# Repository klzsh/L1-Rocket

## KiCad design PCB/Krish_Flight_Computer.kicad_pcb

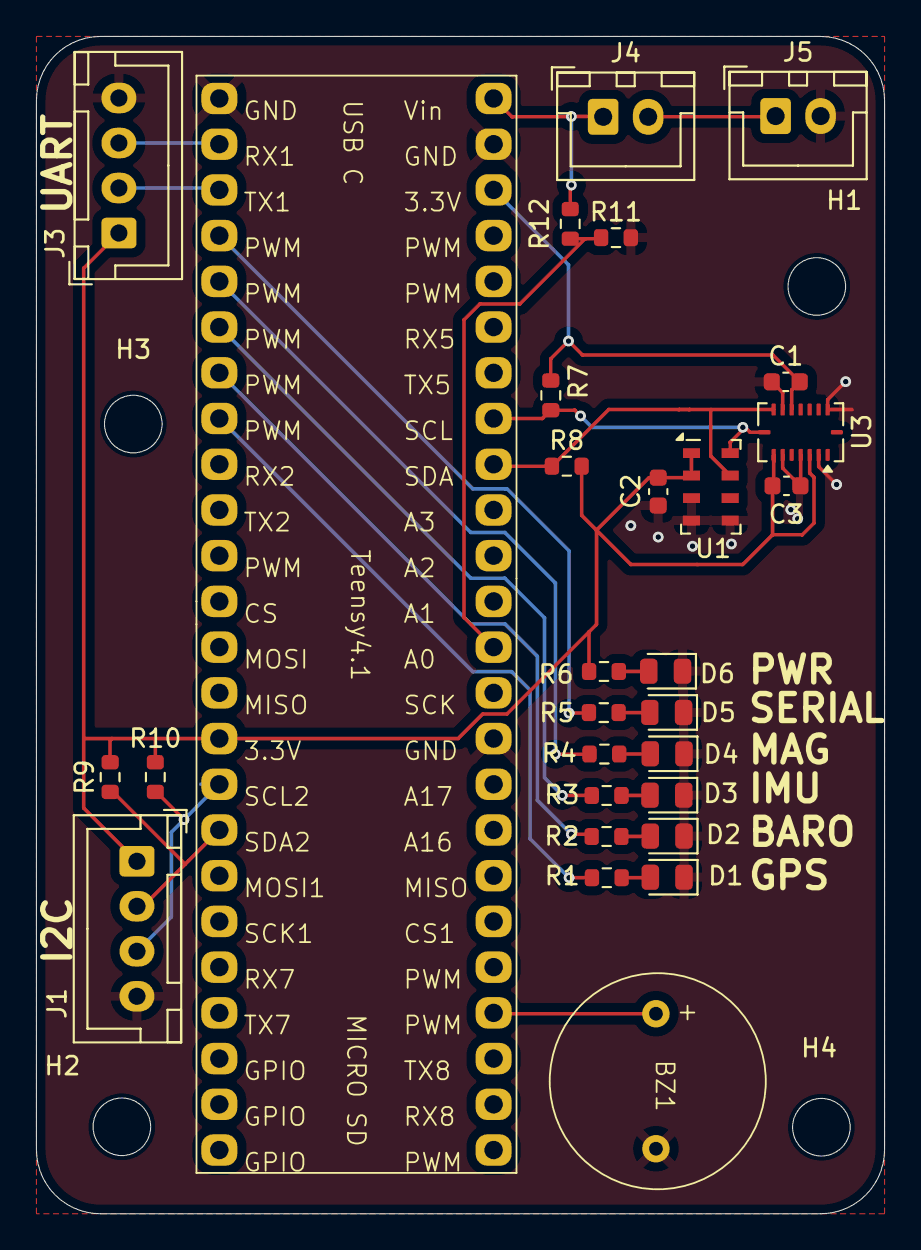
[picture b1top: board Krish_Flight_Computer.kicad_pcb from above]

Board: 2 copper layers, 47.1 x 65.4 mm, 33 parts (0 on the bottom side), 23 nets.

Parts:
BZ1: Buzzer; Adafruit_Buzzer
C1, C2, C3: 100 nF; C_0603_1608Metric
D1: GPS; LED_0805_2012Metric
D2: BARO; LED_0805_2012Metric
D3: IMU; LED_0805_2012Metric
D4: MAG; LED_0805_2012Metric
D5: SRL; LED_0805_2012Metric
D6: PWR; LED_0805_2012Metric
H1, H2, H3, H4: MountingHole; MountingHole_3.2mm_M3
J1: I2C; JST_XH_B4B-XH-A_1x04_P2.50mm_Vertical
J3: UART; JST_XH_B4B-XH-A_1x04_P2.50mm_Vertical
J4: SW; JST_XH_B2B-XH-A_1x02_P2.50mm_Vertical
J5: BAT; JST_XH_B2B-XH-A_1x02_P2.50mm_Vertical
R1, R2, R3, R4, R5, R6: 560; R_0603_1608Metric
R7, R8, R9, R10: 5k1; R_0603_1608Metric
R11: 100k; R_0603_1608Metric
R12: 78k7; R_0603_1608Metric
Teensy4.1: teensy
U1: MS5611-01BA; LGA-8_3x5mm_P1.25mm
U3: BMI088; Bosch_LGA-16_4.5x3mm_P0.5mm_LayoutBorder7x1y_ClockwisePinNu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

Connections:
+3V3: C1.2, C2.1, C3.1, J1.1, J3.1, R6.1, R7.2, R8.2, R9.2, R10.2, Teensy4.1.3V (3.3V), Teensy4.1.3V1 (3.3V), U1.1 (VDD), U1.2 (PS), U3.3 (VDD), U3.7 (PS), U3.11 (VDDIO)
/BARO_LED: R2.1, Teensy4.1.5 (PWM)
/GPS_LED: R1.1, Teensy4.1.6 (PWM)
/IMU_LED: R3.1, Teensy4.1.4 (PWM)
/MAG_LED: R4.1, Teensy4.1.3 (PWM)
/RX: J3.3, Teensy4.1.0 (RX1)
/SCLK2: J1.3, R10.1, Teensy4.1.24 (SCL2)
/SDA2: J1.2, R9.1, Teensy4.1.25 (SDA2)
/SERIAL_LED: R5.1, Teensy4.1.2 (PWM)
/TX: J3.2, Teensy4.1.1 (TX1)
/VBAT: J4.1, R12.2, Teensy4.1.5V (VIN)
GND: BZ1.2 (-), C1.1, C2.2, C3.2, D1.1 (K), D2.1 (K), D3.1 (K), D4.1 (K), D5.1 (K), D6.1 (K), J1.4, J3.4, J5.2, R11.2, Teensy4.1.G (GND), Teensy4.1.G1 (GND), Teensy4.1.G2 (GND), U1.3 (GND), U1.4 (CSB), U1.5 (CSB), U3.2 (GNDA), U3.4 (GNDA), U3.6 (GNDIO), U3.10 (SDO2), U3.15 (SDO1)
unnamed: BZ1.1 (+), Teensy4.1.36 (PWM)
unnamed: D1.2 (A), R1.2
unnamed: D2.2 (A), R2.2
unnamed: D3.2 (A), R3.2
unnamed: D4.2 (A), R4.2
unnamed: D5.2 (A), R5.2
unnamed: D6.2 (A), R6.2
unnamed: J4.2, J5.1
unnamed: R11.1, R12.1, Teensy4.1.14 (A0)
SCLK: R7.1, Teensy4.1.19 (SCL), U1.8 (SCLK), U3.8 (SCK/SCL)
SDA: R8.1, Teensy4.1.18 (SDA), U1.7 (SDI/SDA), U3.9 (SDI/SDA)

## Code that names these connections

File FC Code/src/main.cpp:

#include <Arduino.h>

#include "sensors/baro.h"
#include "sensors/gps.h"
#include "sensors/imu.h"
#include "sensors/batteryVoltage.h"

#include "scheduler/scheduler.h"

#include "radio/radioInterface.h"
#include "scheduler/loopTasks.h"
#include "logging/logger.h"

#include "Mahony.h"
#include "StateEstimation/KalmanFilter.h"

MahonyAHRS AHRS;
SixStateLKF kFilter;

void setup(void)
{
  initLogger(micros());

  pinMode(GPS_LED, OUTPUT);
  pinMode(IMU_LED, OUTPUT);
  pinMode(BARO_LED, OUTPUT);
  pinMode(EXTRA_LED, OUTPUT);
  pinMode(SERIAL_LED, OUTPUT);

  // USB Serial
  Serial.begin(115200);
  logToBuffer("Started Serial", micros());
  if (CrashReport)
  {
    Serial.print(CrashReport);
  }

  // init serial for radio
  RADIO_UART.begin(115200);
  logToBuffer("Started Serial to radio", micros());

  // IMU and Baro
  INTERNAL_I2C_BUS.begin();
  INTERNAL_I2C_BUS.setClock(400000UL);
  logToBuffer("Started internal I2C bus", micros());

  // GPS
  EXTERNAL_I2C_BUS.begin();
  EXTERNAL_I2C_BUS.setClock(400000UL);
  logToBuffer("Started external I2C bus", micros());

  bool GPSStatus = initGPS();
  logToBuffer(GPSStatus ? "GPS Init" : "GPS Init Failed", micros());

  analogWrite(GPS_LED, 128);
  while (!calculateInitialGPSCoords())
  {
  }
  digitalWrite(GPS_LED, HIGH);

  bool baroStatus = initBaro();
  logToBuffer(baroStatus ? "Baro Init" : "Baro Init Failed", micros());
  digitalWrite(BARO_LED, HIGH);

  bool IMUStatus = initBMI088();
  logToBuffer(IMUStatus ? "IMU Init" : "IMU Init Failed", micros());
  digitalWrite(IMU_LED, HIGH);

  initVoltageSensor();
  logToBuffer("Voltage Sens Init", micros());

  bool radioStatus = initRadio();
  logToBuffer(radioStatus ? "Radio Init" : "Radio Init Failed", micros());
  clearQueue();
  logToBuffer("Queue Cleared", micros());

  initScheduler();
  logToBuffer("Initialized Scheduler", micros());

  AHRS.setMode(MahonyMode::CALIBRATING);
  const int calibSamples = 200;
  for (int i = 0; i < calibSamples; i++)
  {
    // Assume ~100Hz for the delay(10) loop
    floatVector_3 accelOutput = {0,0,0};
    readAccelData(&accelOutput);
    Vector<3> accel = Vector<3>(accelOutput.x, accelOutput.y, accelOutput.z);

    floatVector_3 gyroOutput = {0,0,0};
    readGyroData(&gyroOutput);
    Vector<3> gyro = Vector<3>(gyroOutput.x, gyroOutput.y, gyroOutput.z);
    AHRS.update(accel, gyro, 0.01);
    delay(10);
  }
  AHRS.finalizeCalibration();
  initializeRocketState();

  logToBuffer("====Starting Scheduler Loop====", micros());
  writeToDisk(micros());
}

void loop(void)
{
  schedulerLoop();

}

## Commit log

2025-11-26 PCB Files
2025-12-06 removed MMC5603
2025-12-31 added openrocket sim
2025-12-31 Nosecone CAD
2025-12-31 Kalman filter tuning code from TRT/Kalman-Filter
2026-01-11 started on the (hella bad) FC Code
2026-01-11 fixed matlab script
2026-02-01 chatgpted a data plotter
2026-02-03 used kalman filter and AHRS from TRT/Astra instead of my shitty implementation
2026-03-08 rewrote the code to use Astra rocket
2026-03-08 MDRA ESL321 launch edits
